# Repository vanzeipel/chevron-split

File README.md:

# chevron-split
A split, column-staggered mechanical keyboard where the key layout forms something of a chevron shape that more closely follows the natural resting position of the fingers. 52-key layout with 3 thumb keys and a rotary knob on the right half. Uses the Pro Micro Elite-C controller as the primary controller and any compatible Pro Micro as the secondary controller on the other half.
## Getting Started
All the files you'll need to fabricate the keyboard's PCB and 3D printed case are included in the `/pcbs` and `/cases` directories. You can use them to print your 3D case and upload the BOM to get a PCB printed.
### Making Layout Changes
If you want to make any adjustments to the layout, you'll need to generate new outlines and PCB files.
### Setup
1. Make sure Node.js Package Manager `npm` is installed.
2. Run `npm install` to install the required packages defined in `package.json`.
3. Run `npm run patch-footprints` to make the custom PCB component footprints available to the local `ergogen` package.
### Rebuilding the Layout
1. Modify `/layout/config.yaml`
2. Run `npm run gen` to invoke `ergogen` on the `/layout/config.yaml` to build the outlines and basic PCB files, located in the `/output` directory.

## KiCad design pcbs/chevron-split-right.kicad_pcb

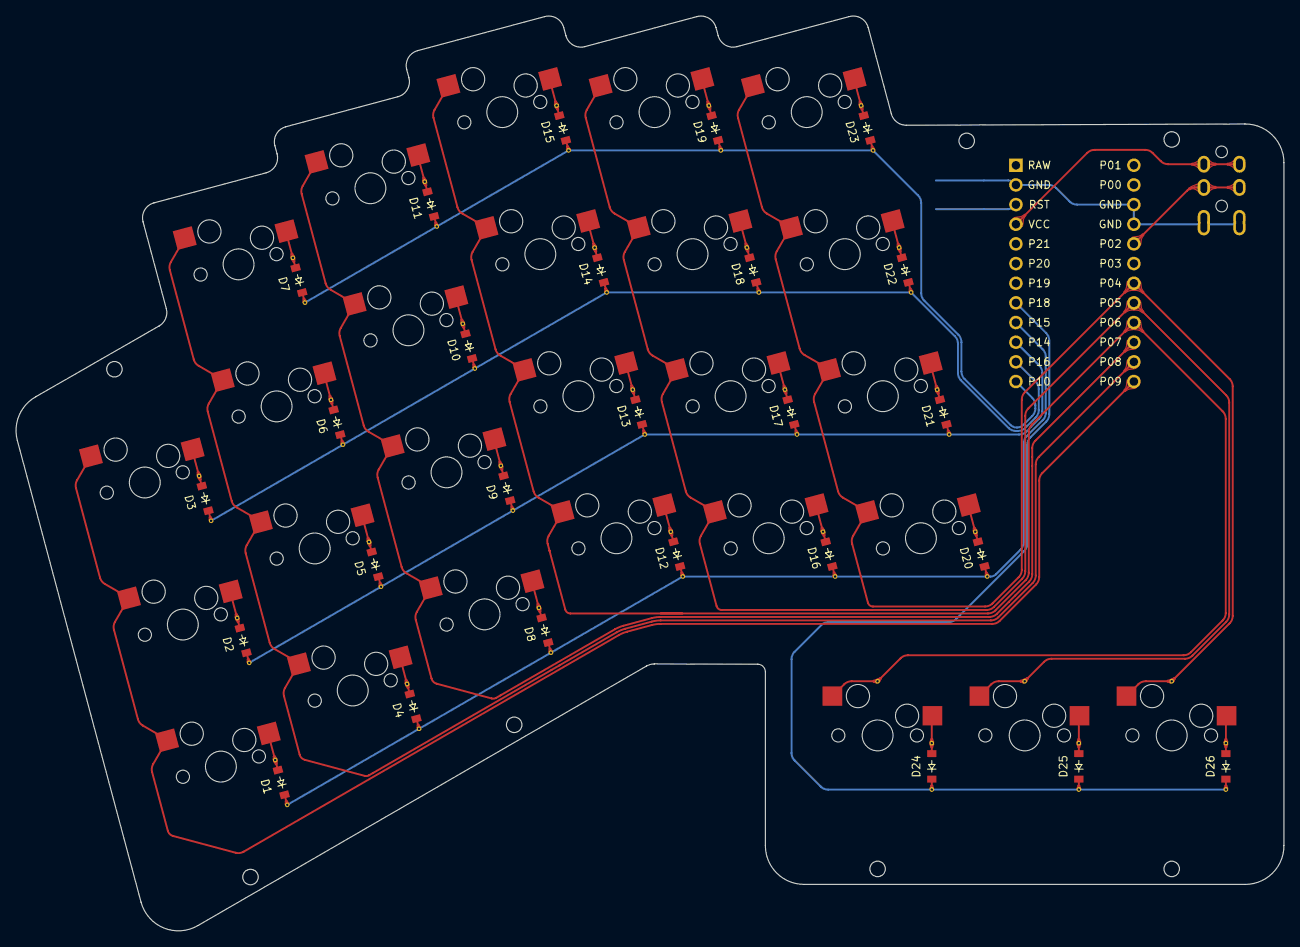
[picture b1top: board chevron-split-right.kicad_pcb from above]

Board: 2 copper layers, 163.8 x 118.2 mm, 54 parts (0 on the bottom side), 39 nets.

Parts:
B1: SW_TACT_ALPS_SKQGABE010
D1, D2, D3, D4, D5, D6, D7, D8, D9, D10, D11, D12, D13, D14, D15, D16, D17, D18, D19, D20, D21, D22, D23, D24, D25, D26: SOD-123_Right
MCU1: ProMicro
S1, S2, S3, S4, S5, S6, S7, S8, S9, S10, S11, S12, S13, S14, S15, S16, S17, S18, S19, S20, S21, S22, S23, S24, S25, S26: MX_1U_HotSocket_Right

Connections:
GND: B1.1, MCU1.2, MCU1.15, MCU1.16
P4: MCU1.19, S20.2, S21.2, S22.2, S23.2, S26.2
P5: MCU1.20, S16.2, S17.2, S18.2, S19.2, S25.2
P6: MCU1.21, S12.2, S13.2, S14.2, S15.2, S24.2
P7: MCU1.22, S8.2, S9.2, S10.2, S11.2
P8: MCU1.23, S4.2, S5.2, S6.2, S7.2
P9: MCU1.24, S1.2, S2.2, S3.2
P10: D7.1, D11.1, D15.1, D19.1, D23.1, MCU1.12
P14: D2.1, D5.1, D9.1, D13.1, D17.1, D21.1, MCU1.10
P15: D1.1, D4.1, D8.1, D12.1, D16.1, D20.1, MCU1.9
P16: D3.1, D6.1, D10.1, D14.1, D18.1, D22.1, MCU1.11
P18: D24.1, D25.1, D26.1, MCU1.8
RST: B1.2, MCU1.3
far_thumb: D26.2, S26.1
home_thumb: D25.2, S25.1
index_home: D17.2, S17.1
index_lower: D16.2, S16.1
index_number: D19.2, S19.1
index_upper: D18.2, S18.1
inner_home: D21.2, S21.1
inner_lower: D20.2, S20.1
inner_number: D23.2, S23.1
inner_upper: D22.2, S22.1
middle_home: D13.2, S13.1
middle_lower: D12.2, S12.1
middle_number: D15.2, S15.1
middle_upper: D14.2, S14.1
near_thumb: D24.2, S24.1
outer_home: D2.2, S2.1
outer_lower: D1.2, S1.1
outer_upper: D3.2, S3.1
pinky_home: D5.2, S5.1
pinky_lower: D4.2, S4.1
pinky_number: D7.2, S7.1
pinky_upper: D6.2, S6.1
ring_home: D9.2, S9.1
ring_lower: D8.2, S8.1
ring_number: D11.2, S11.1
ring_upper: D10.2, S10.1

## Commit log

2022-06-20 Added initial ergogen layout configuration.
2022-07-06 Added case outlines and redefined the layout to be absolutely precise with rounded corners.
2022-07-10 Added PCB and footprints for MCU and TRRS
2022-11-11 Prototype version 0.1
    Added rotary encoder to the left keyboard. Altered layout to use a 15 degree stagger instead of a 1/4 stagger (which was 14.03 degrees, harder to work with). Added footprints for surface-mount diodes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
2022-11-15 Missed changes to layout.yaml and package.json in the previous commit
2023-05-16 Enlarged screw holes to 2.0mm so M2 screws can be used instead of M1.6
2023-05-16 Updated README and removed Windows-specific node packageas WSL2 provides a better Windows/Linux integration
2024-11-11 Snapshot of files for manufacturing prototype version 0.1 PCBs. Created left and right versions for faster prototype iteration.
2024-11-11 Restore README.md with information on how to rebuild the layout.
